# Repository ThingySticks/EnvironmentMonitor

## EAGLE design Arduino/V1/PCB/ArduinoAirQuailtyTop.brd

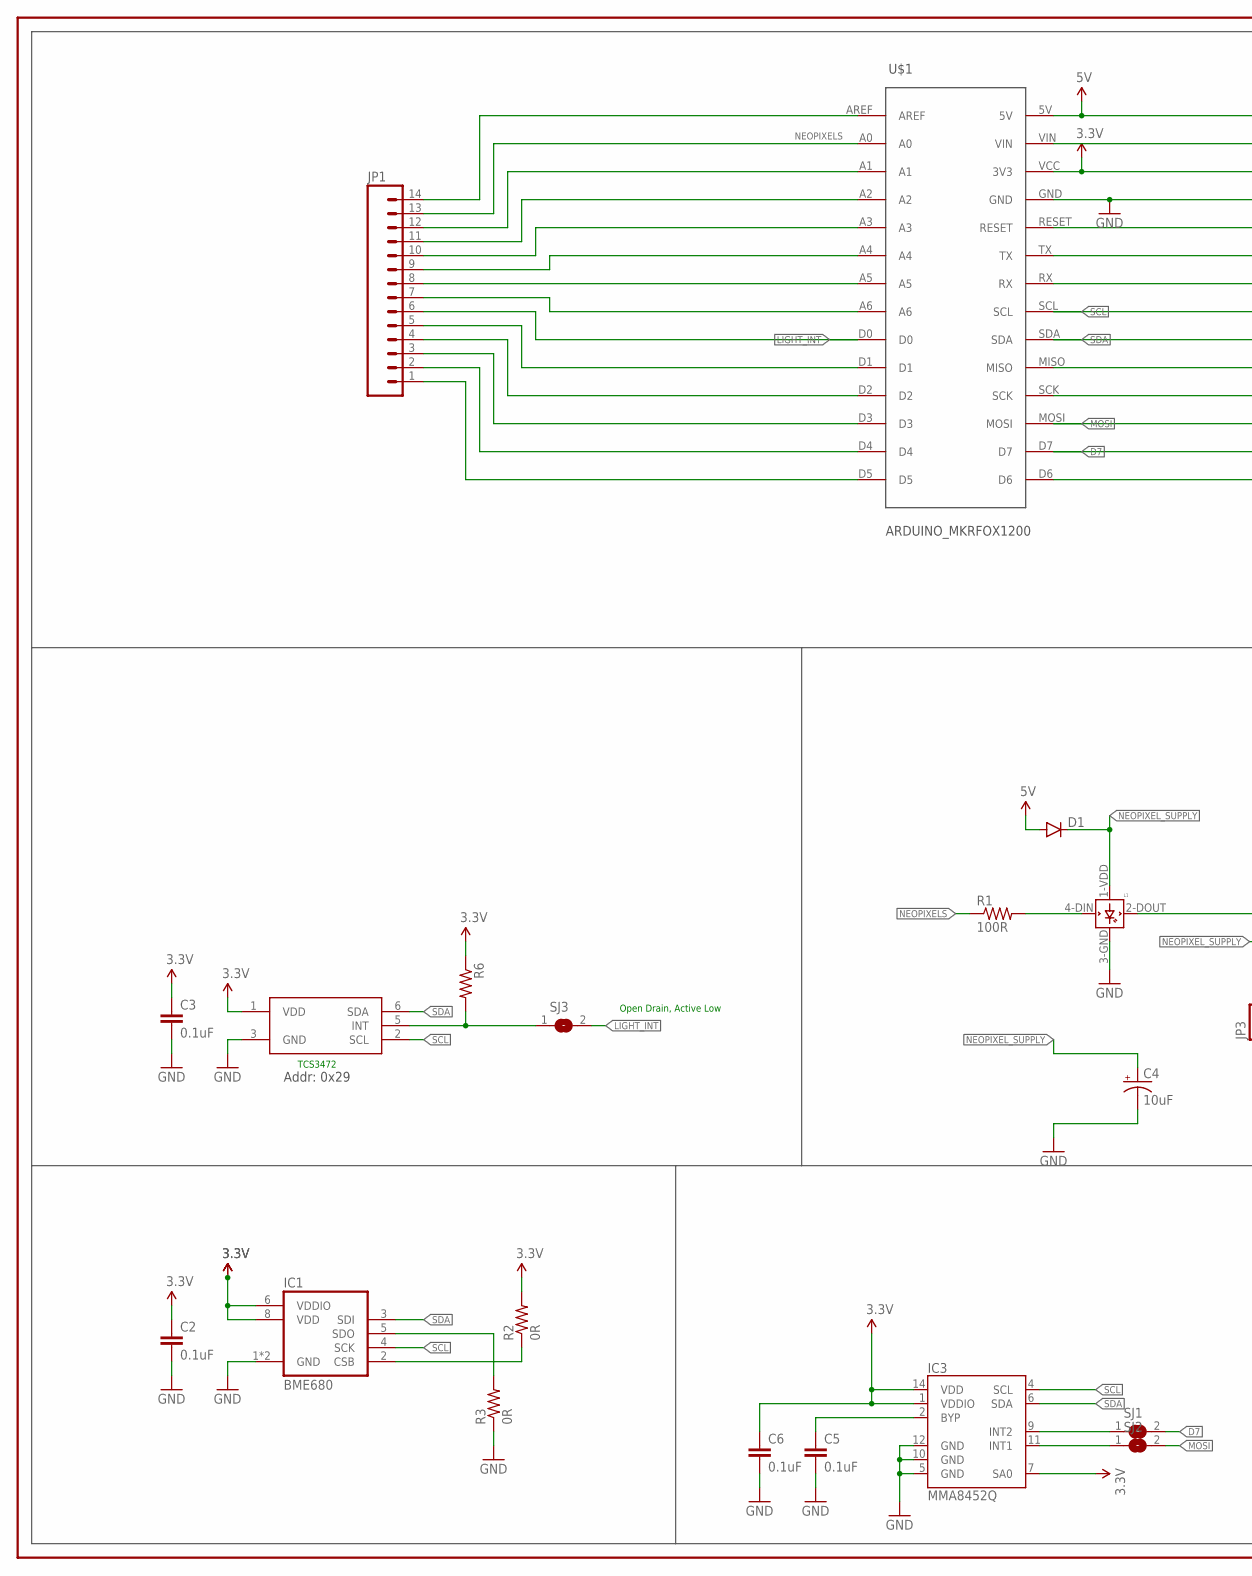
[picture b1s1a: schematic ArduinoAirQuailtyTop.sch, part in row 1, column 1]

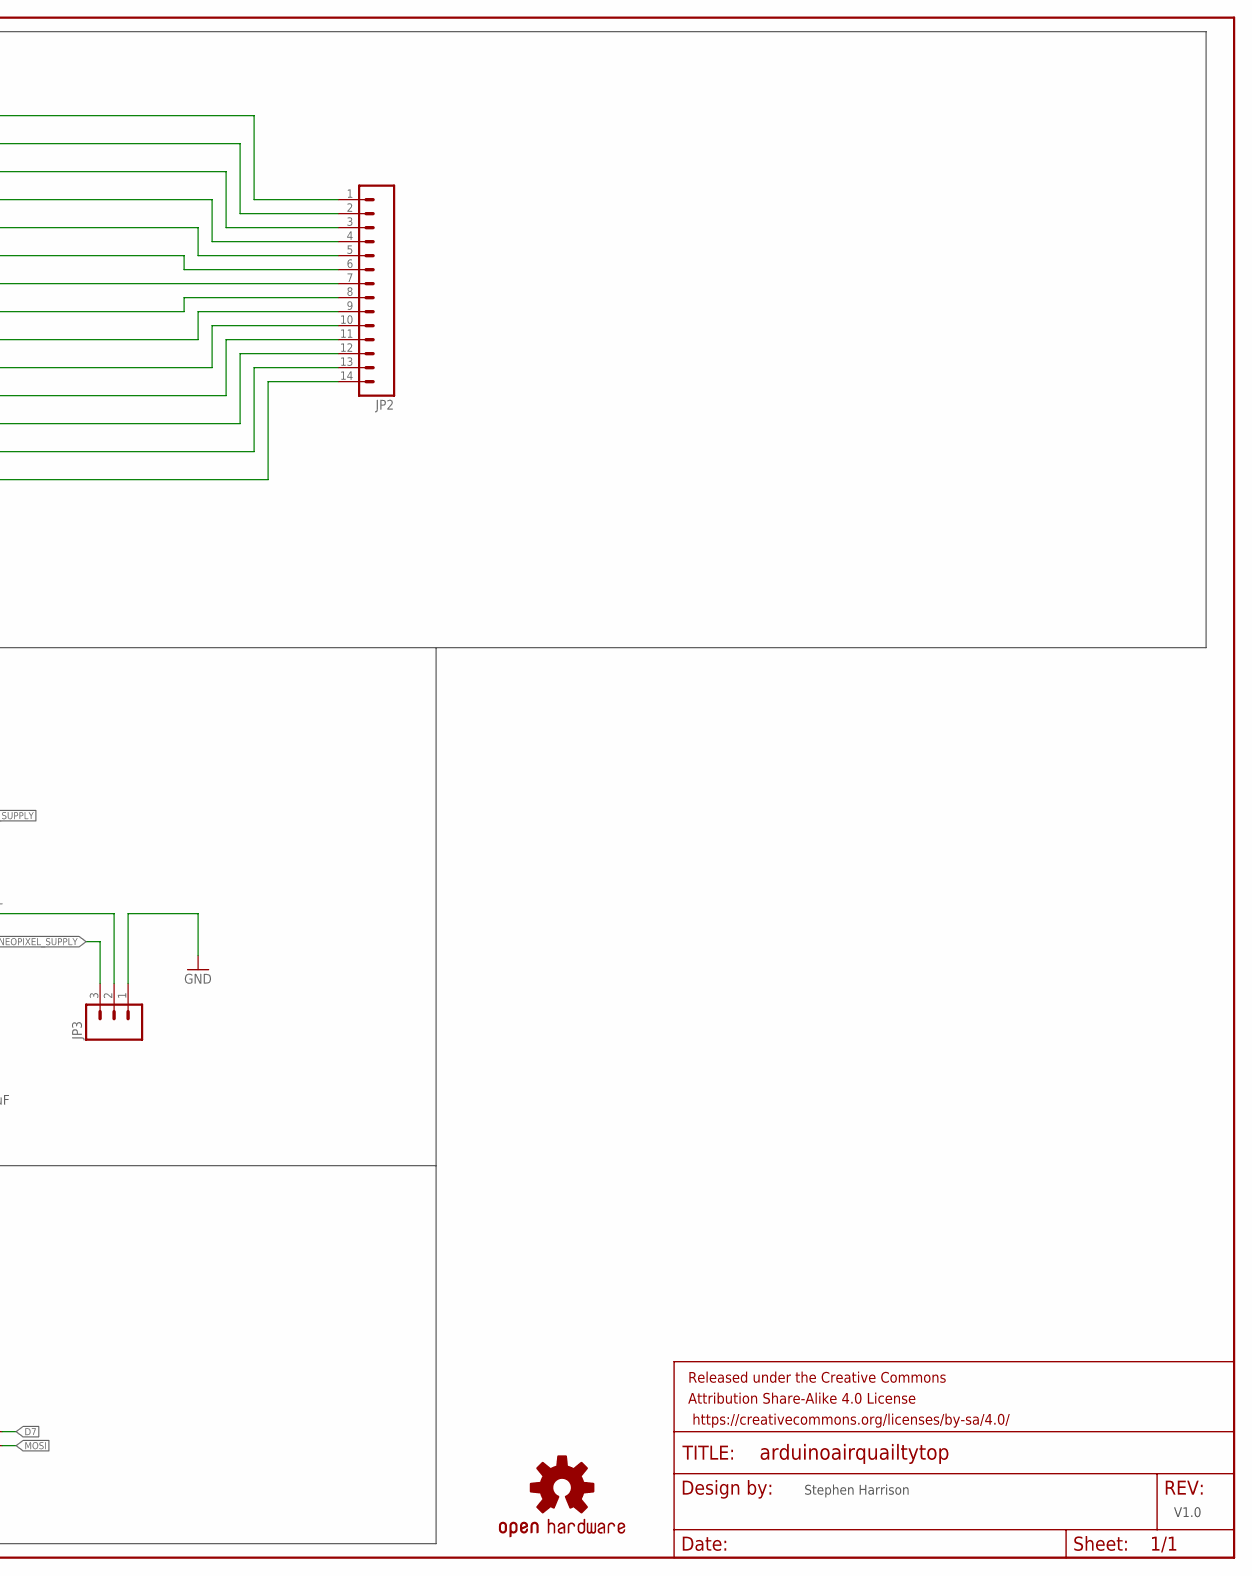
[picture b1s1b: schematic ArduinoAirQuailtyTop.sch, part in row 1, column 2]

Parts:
C2, C3, C5, C6: 0.1uF; 0805
C4: 10uF; EIA3216
D1: DIODESMA; SMA-DIODE
FRAME1: FRAME-LEDGER; CREATIVE_COMMONS
IC1: BME680; MOUSER 262-BME680
IC2: TCS34725FN; FN-6; MOUSER 985-TCS34725FN
IC3: MMA8452Q; QFN-16_0.5MM; MOUSER 841-MMA8452QT
JP1, JP2: M14; 1X14
JP3: M03POLAR; MOLEX-1X3
L1: WS2812B
LOGO1: OSHW-LOGOM; OSHW-LOGO-M
R1: 100R; 0805
R2, R3: 0R; 0805
R6: RESISTOR0805-RES; 0805
SJ1, SJ2, SJ3: SJ
U$1: ARDUINO_MKRFOX1200

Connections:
3.3V: C2.1, C3.1, C6.1, IC1.6 (VDDIO), IC1.8 (VDD), IC2.1 (VDD), IC3.1 (VDDIO), IC3.7 (SA0), IC3.14 (VDD), JP2.3, R2.2, R6.1, U$1.VCC (3V3)
5V: D1.A, JP2.1, U$1.5V
D7: JP2.13, SJ1.2, U$1.D7
GND: C2.2, C3.2, C4.C (-), C5.2, C6.2, IC1.1 (GND), IC1.7 (GND), IC2.3 (GND), IC3.5 (GND), IC3.10 (GND), IC3.12 (GND), JP2.4, JP3.1, L1.3-GND (GND), R3.1, U$1.GND
LIGHT_INT: JP1.6, SJ3.2, U$1.D0
MOSI: JP2.12, SJ2.2, U$1.MOSI
unnamed: IC3.9 (INT2), SJ1.1
unnamed: IC3.11 (INT1), SJ2.1
unnamed: JP1.1, U$1.D5
unnamed: JP1.2, U$1.D4
unnamed: JP1.3, U$1.D3
unnamed: C5.1, IC3.2 (BYP)
unnamed: JP1.4, U$1.D2
unnamed: JP1.5, U$1.D1
unnamed: JP1.7, U$1.A6
unnamed: JP1.8, U$1.A5
unnamed: JP1.9, U$1.A4
unnamed: JP1.10, U$1.A3
unnamed: JP1.11, U$1.A2
unnamed: JP1.12, U$1.A1
unnamed: JP1.14, U$1.AREF
unnamed: JP2.14, U$1.D6
unnamed: JP2.11, U$1.SCK
unnamed: JP2.10, U$1.MISO
unnamed: JP2.7, U$1.RX
unnamed: JP2.6, U$1.TX
unnamed: JP2.5, U$1.RESET
unnamed: JP2.2, U$1.VIN
unnamed: IC1.5 (SDO), R3.2
unnamed: IC1.2 (CSB), R2.1
unnamed: IC2.5 (INT), R6.2, SJ3.1
unnamed: L1.4-DIN (DIN), R1.2
unnamed: JP3.2, L1.2-DOUT (DOUT)
NEOPIXELS: JP1.13, R1.1, U$1.A0
NEOPIXEL_SUPPLY: C4.A (+), D1.C, JP3.3, L1.1-VDD (VDD)
SCL: IC1.4 (SCK), IC2.2 (SCL), IC3.4 (SCL), JP2.8, U$1.SCL
SDA: IC1.3 (SDI), IC2.6 (SDA), IC3.6 (SDA), JP2.9, U$1.SDA

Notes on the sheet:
TCS3472
Open Drain, Active Low
Stephen Harrison
V1.0
Addr: 0x29

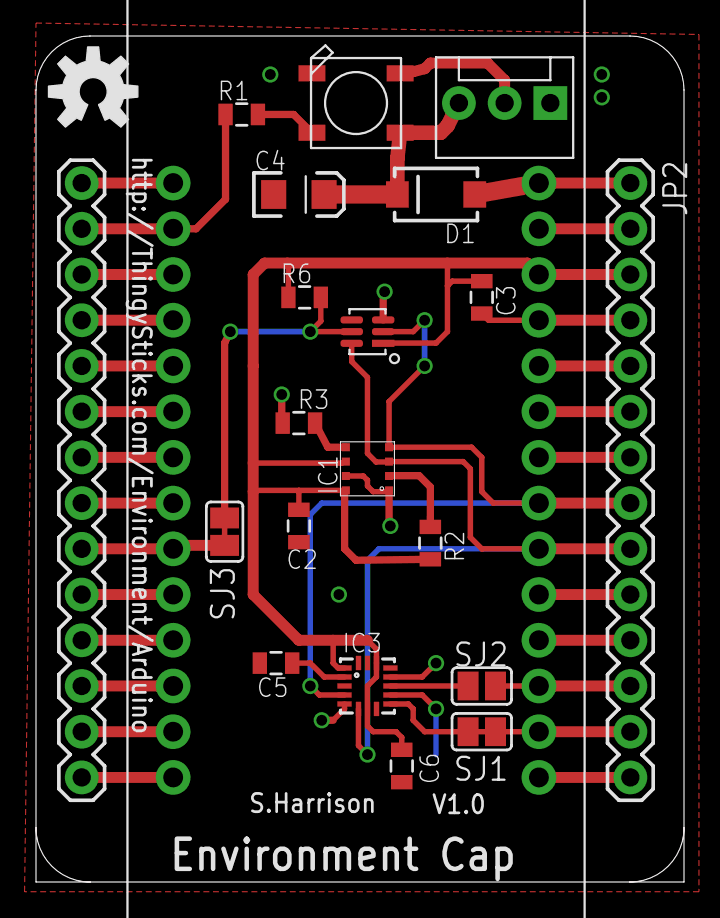
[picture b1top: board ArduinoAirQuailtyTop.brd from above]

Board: 2 copper layers, 36.0 x 47.0 mm, 23 parts (0 on the bottom side), 37 nets.

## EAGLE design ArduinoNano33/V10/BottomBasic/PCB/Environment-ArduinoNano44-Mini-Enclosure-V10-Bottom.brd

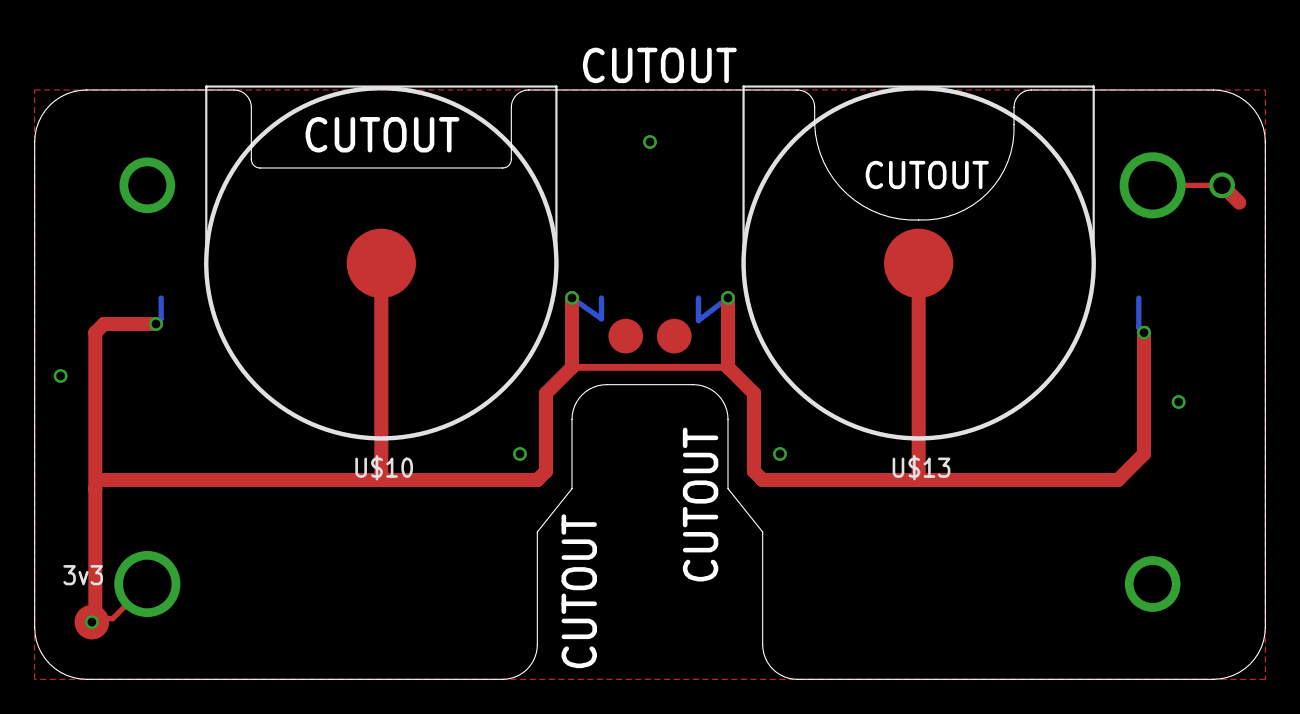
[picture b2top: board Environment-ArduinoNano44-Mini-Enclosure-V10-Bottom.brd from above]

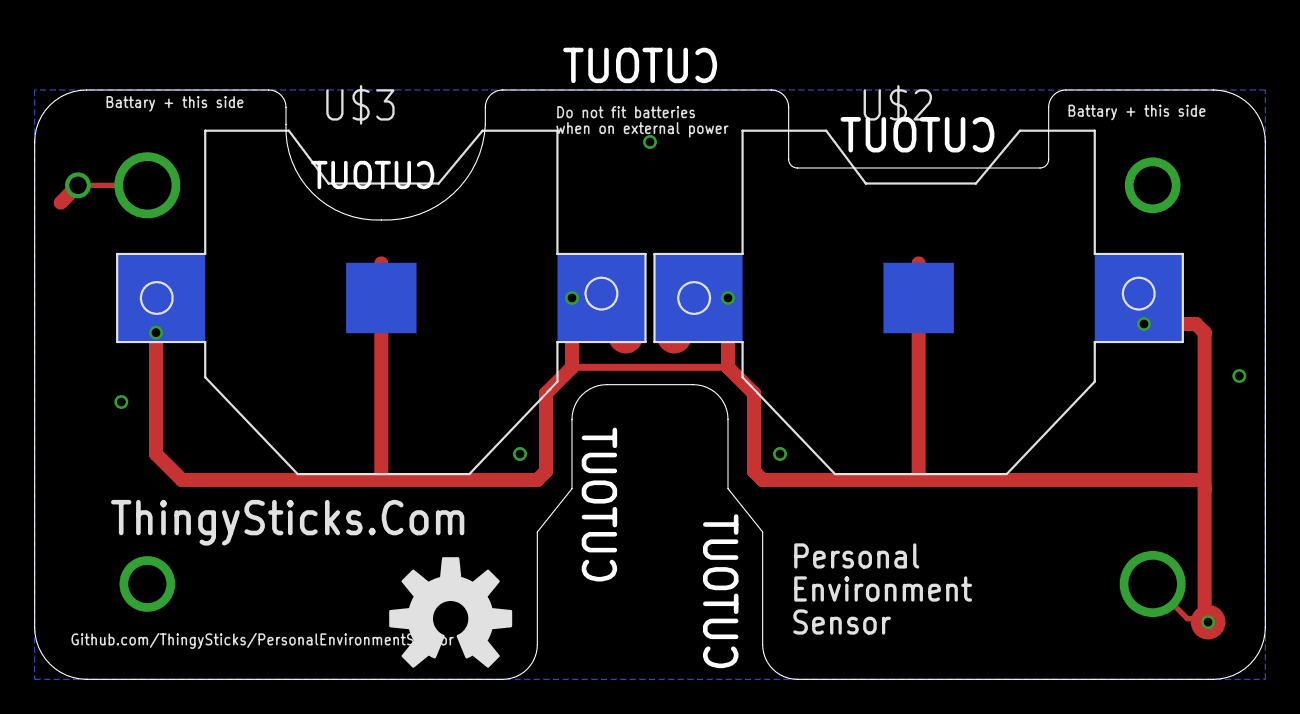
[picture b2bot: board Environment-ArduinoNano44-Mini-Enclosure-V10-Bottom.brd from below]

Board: 2 copper layers, 71.0 x 34.0 mm, 5 parts (5 on the bottom side), 2 nets.

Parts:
LOGO3: OSHW-LOGOL; OSHW-LOGO-L
U$2, U$3: CR2032-SMD
U$10, U$13: CR2032-SPLIT-PCB-POSITIVE; CR2032-SMD-POSITIVE-TERMINAL

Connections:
3.3V: U$2.+$1, U$2.+$2, U$3.+$1, U$3.+$2, U$10.+, U$13.+
GND: U$2.-, U$3.-

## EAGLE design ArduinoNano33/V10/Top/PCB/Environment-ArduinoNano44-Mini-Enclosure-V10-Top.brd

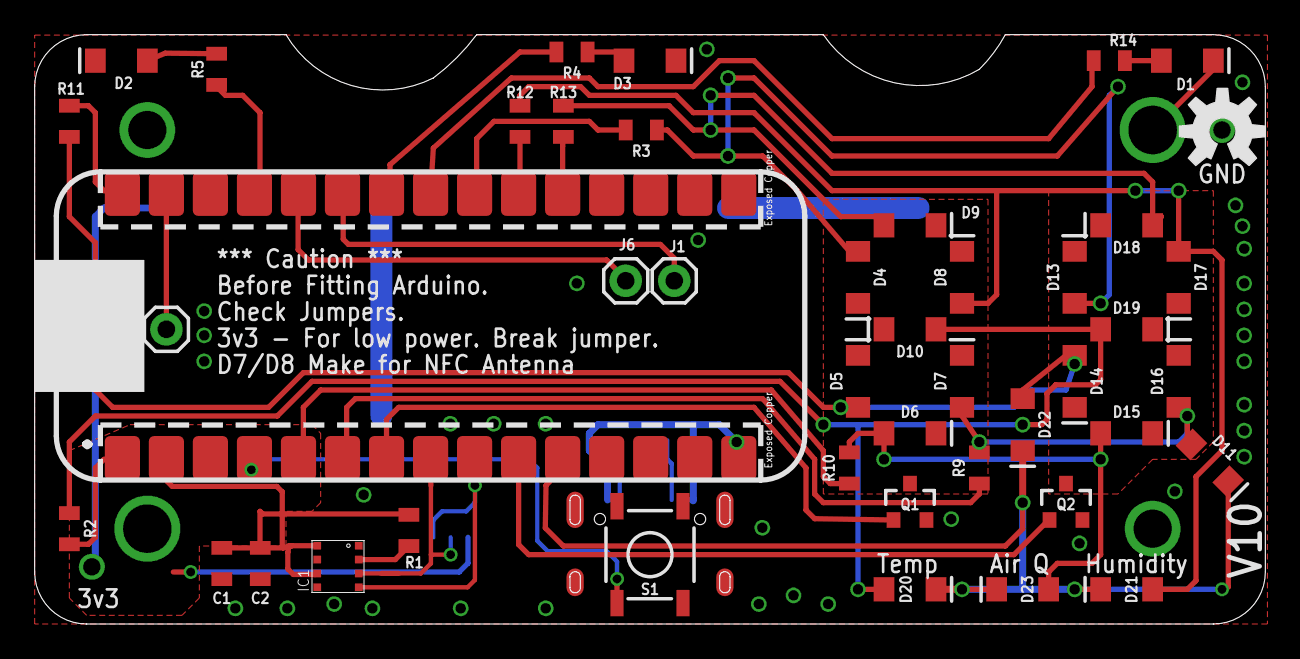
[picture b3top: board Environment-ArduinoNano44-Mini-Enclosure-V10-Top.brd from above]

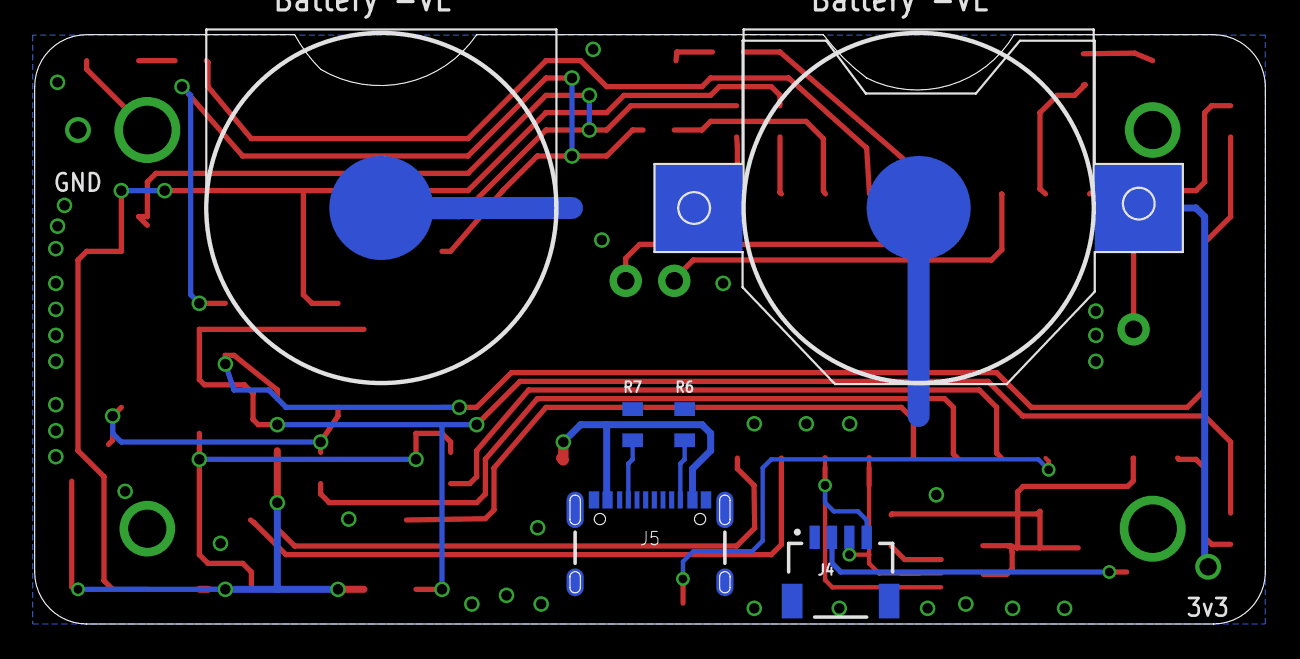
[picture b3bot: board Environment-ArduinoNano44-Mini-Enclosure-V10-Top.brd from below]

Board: 2 copper layers, 71.0 x 34.0 mm, 51 parts (7 on the bottom side), 37 nets.

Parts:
C1: 0.1uF; 0805
C2: 1.0uF; 0805
D1: Red; LED-1206
D2: Yellow; LED-1206
D3, D20, D21, D23: Green; LED-1206
D4, D5, D6, D7, D8, D9, D10, D11, D13, D14, D15, D16, D17, D18, D19, D22: Blue; LED-1206
IC1: BME680
J1, J3, J6: 1X01
J4: QUIC; JST04_1MM_RA
J5: USB-C-16P
LOGO1: OSHW-LOGOM; OSHW-LOGO-M
Q1, Q2: 5.8A/30V/35mΩ; SOT23-3
R1: 10k; 0805
R2, R3, R4, R5, R9, R10, R11, R12, R13, R14: 1k5; 0805
R6, R7: 5k1; 0805
S1: MOMENTARY-SWITCH-SPST-SMD-5.2MM; TACTILE_SWITCH_SMD_5.2MM
U$1: ARDUINO_33_NANOARDUINO_NANO_33_BLE_SENSE_SMD; ARDUINO_NANO_33_SMD
U$6: CR2032-SMD
U$8, U$9: CR2032-SPLIT-PCBCR2032-NEGATIVE; CR2032-SMD-NEGATIVE-TERMINAL

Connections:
3.3V: C1.1, C2.1, IC1.6, IC1.8, J4.2, R1.2, U$1.@2, U$6.+$2
A: D9.A, D18.A, R13.1
A0: S1.1, U$1.@4
B: D8.A, D17.A, D21.A, R12.1
C: D7.A, D11.A, D16.A, R9.2
CC1: J5.A5, R7.1
CC2: J5.B5, R6.1
D: D6.A, D15.A, D23.A, R10.2
DIGIT1: D4.C, D5.C, D6.C, D7.C, D8.C, D9.C, D10.C, Q1.3
DIGIT1_SELECT: Q1.1, U$1.@7
DIGIT2: D13.C, D14.C, D15.C, D16.C, D17.C, D18.C, D19.C, Q2.3
DIGIT2_SELECT: Q2.1, U$1.@10
DIGIT3: D11.C, D20.C, D21.C, D22.C, D23.C, U$1.@11
E: D5.A, D14.A, D22.A, R11.1
F: D4.A, D13.A, R3.1
G: D10.A, D19.A, D20.A, R2.1
GND: C1.2, C2.2, D1.C, D2.C, D3.C, IC1.1, IC1.5, IC1.7, J4.1, J5.GND, J5.GND2, Q1.2, Q2.2, R6.2, R7.2, S1.3, U$1.@14, U$1.@19, U$6.-, U$8.-, U$9.-
GREEN: R4.2, U$1.@24
unnamed: IC1.2, R1.1
unnamed: D1.A, R14.1
unnamed: R9.1, U$1.@6
unnamed: R2.2, U$1.1
unnamed: R11.2, U$1.@30
unnamed: R12.2, U$1.@21
unnamed: R10.1, U$1.@5
unnamed: R13.2, U$1.@20
unnamed: R3.2, U$1.@22
unnamed: D3.A, R4.1
unnamed: D2.A, R5.1
unnamed: J3.1, U$1.@29
NCF_ANTENNA1: J6.1, U$1.@26
NCF_ANTENNA2: J1.1, U$1.@25
RED: R14.2, U$1.@23
SCL: IC1.4, J4.4, U$1.@9
SDA: IC1.3, J4.3, U$1.@8
VIN: J5.VBUS1, J5.VBUS2, U$1.@15
YELLOW: R5.2, U$1.@27

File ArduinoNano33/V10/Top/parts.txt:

Partlist

Exported from Environment-ArduinoNano33-V10.1-Top.brd at 27/02/2020 07:29

EAGLE Version 7.4.0 Copyright (c) 1988-2015 CadSoft

Assembly variant: 

Part     Value                                             Package                        Library                        Position (mm)         Orientation

C1       0.1uF                                             0805                           ThingySticks                   (10.795 3.4925)       R270
C2       1.0uF                                             0805                           ThingySticks                   (13.0175 3.4925)      R270
D1       Red                                               LED-1206                       ThingySticks                   (66.5 32.5)           R0
D2       Green                                             LED-1206                       ThingySticks                   (5 32.5)              R180
D3       Yellow                                            LED-1206                       ThingySticks                   (35.5 32.5)           R0
D4       Blue                                              LED-1206                       ThingySticks                   (47.5 20)             R270
D5       Blue                                              LED-1206                       ThingySticks                   (47.5 14)             R90
D6       Blue                                              LED-1206                       ThingySticks                   (50.5 11)             R0
D7       Blue                                              LED-1206                       ThingySticks                   (53.5 14)             R90
D8       Blue                                              LED-1206                       ThingySticks                   (53.5 20)             R90
D9       Blue                                              LED-1206                       ThingySticks                   (50.5 23)             R0
D10      Blue                                              LED-1206                       ThingySticks                   (50.5 17)             R180
D11      Blue                                              LED-1206                       ThingySticks                   (67.8 9.3)            R315
D13      Blue                                              LED-1206                       ThingySticks                   (60 20)               R90
D14      Blue                                              LED-1206                       ThingySticks                   (60 14)               R270
D15      Blue                                              LED-1206                       ThingySticks                   (63 11)               R0
D16      Blue                                              LED-1206                       ThingySticks                   (66 14)               R90
D17      Blue                                              LED-1206                       ThingySticks                   (66 20)               R270
D18      Blue                                              LED-1206                       ThingySticks                   (63 23)               R180
D19      Blue                                              LED-1206                       ThingySticks                   (63 17)               R0
D20      Green                                             LED-1206                       ThingySticks                   (50.5 2)              R0
D21      Green                                             LED-1206                       ThingySticks                   (63 2)                R180
D22      Blue                                              LED-1206                       ThingySticks                   (57 11.5)             R270
D23      Green                                             LED-1206                       ThingySticks                   (57 2)                R180
IC1      BME680                                            BME680                         ThingySticks                   (17.5 3.3175)         R90
J1                                                         1X01                           SparkFun-Connectors            (36.9 19.8)           R270
J3                                                         1X01                           SparkFun-Connectors            (7.6 17)              R0
J4       QUIC                                              JST04_1MM_RA                   SparkFun-Connectors-2020-01-17 (24.5 5)              MR0
J6                                                         1X01                           SparkFun-Connectors            (34.1 19.8)           R270
JP1      USB-NEW-MICROB                                    USB-MICROB                     Tinamous                       (35.4 3)              MR0
Q1       5.8A/30V/35m?                                     SOT23-3                        SparkFun-DiscreteSemi          (50.5 7)              R0
Q2       5.8A/30V/35m?                                     SOT23-3                        SparkFun-DiscreteSemi          (59.5 7)              R0
R1       10k                                               0805                           SparkFun-Resistors             (21.59 4.7975)        R90
R2       1k5                                               0805                           SparkFun-Resistors             (2 5.5)               R270
R3       1k5                                               0805                           SparkFun-Resistors             (35 28.8175)          R180
R4       1k5                                               0805                           SparkFun-Resistors             (31 33)               R180
R5       1k5                                               0805                           SparkFun-Resistors             (10.5 32)             R270
R6       200k                                              0805                           SparkFun-Resistors             (27.25 2.25)          R90
R7       100k                                              0805                           SparkFun-Resistors             (29.9 2.95)           R0
R9       1k5                                               0805                           SparkFun-Resistors             (54.5 9)              R90
R10      1k5                                               0805                           SparkFun-Resistors             (47 9)                R90
R11      1k5                                               0805                           SparkFun-Resistors             (2 29)                R90
R12      1k5                                               0805                           SparkFun-Resistors             (28 29)               R270
R13      1k5                                               0805                           SparkFun-Resistors             (30.5 29)             R270
R14      1k5                                               0805                           SparkFun-Resistors             (62 32.5)             R180
U$1      ARDUINO_33_NANOARDUINO_NANO_33_BLE_SENSE_SMD_WIDE ARDUINO_NANO_33_SMD_WIDER_PADS ThingySticks                   (1.25 8.305)          R90
U$6                                                        CR2032-SMD                     ThingySticks                   (20 24)               MR0
U$8      CR2032-SPLIT-PCBCR2032-NEGATIVE                   CR2032-SMD-NEGATIVE-TERMINAL   ThingySticks                   (20 24)               MR0
U$9      CR2032-SPLIT-PCBCR2032-NEGATIVE                   CR2032-SMD-NEGATIVE-TERMINAL   ThingySticks                   (51 24)               MR0

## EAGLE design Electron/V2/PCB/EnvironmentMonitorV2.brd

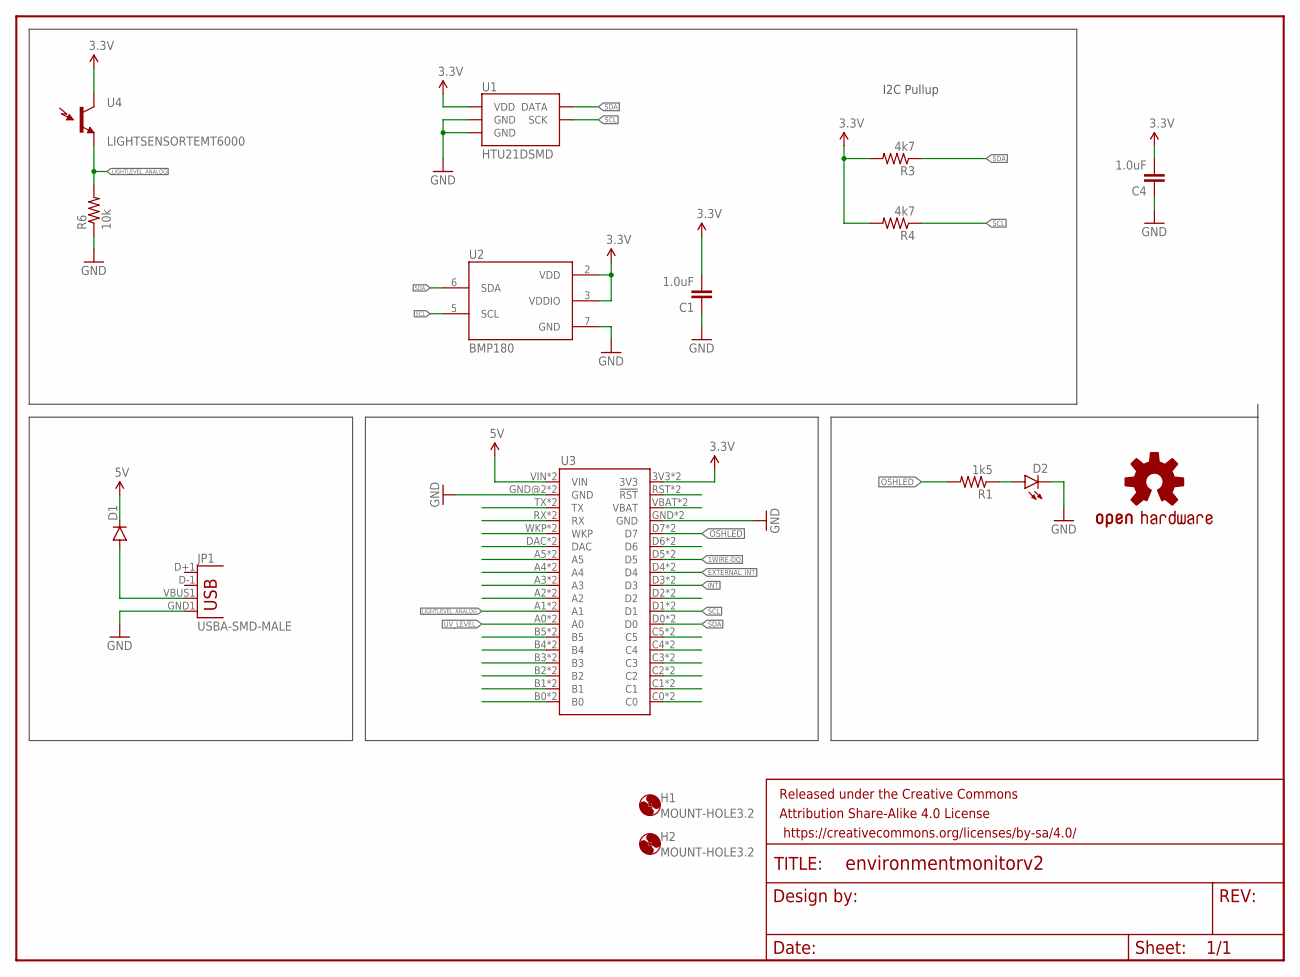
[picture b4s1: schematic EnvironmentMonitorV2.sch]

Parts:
C1, C4: 1.0uF; 0805-CAP
D1: DIODESMA; SMA-DIODE
D2: LED1206-BOTTOM; LED-1206-BOTTOM
FRAME1: FRAME-LETTER; CREATIVE_COMMONS
H1, H2: MOUNT-HOLE3.2; 3,2
JP1: USBA-SMD-MALE; USB-A-SMT-MALE
LOGO1: OSHW-LOGOM; OSHW-LOGO-M
R1: 1k5; 0805
R3, R4: 4k7; 0805
R6: 10k; 0805
U1: HTU21DSMD; HTU21D
U2: BMP180
U3: ELECTRONDUALNAMED; ELECTRON_SIMPLE_SILK_NAMES_DUAL
U4: LIGHTSENSORTEMT6000; TEMT6000-SEN

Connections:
1WIRE-DQ: U3.D5, U3.D5_1 (D5)
3.3V: C1.2, C4.2, R3.2, R4.2, U1.VDD, U2.2 (VDD), U2.3 (VDDIO), U3.3V3, U3.3V3_1 (3V3), U4.COLLECTOR (C1)
5V: D1.C, U3.VIN, U3.VIN_1B (VIN)
EXTERNAL_INT: U3.D4, U3.D4_1 (D4)
GND: C1.1, C4.1, D2.C, JP1.GND1 (GND), R6.1, U1.7 (GND), U1.GND, U2.7 (GND), U3.GND, U3.GND@2 (GND), U3.GND_1 (GND), U3.GND_1B (GND)
INT: U3.D3, U3.D3_1 (D3)
LIGHTLEVEL_ANALOG: R6.2, U3.A1, U3.A1_1 (A1), U4.EMITTER (E1)
unnamed: U3.RST (!RST), U3.RST_1 (!RST)
unnamed: U3.VBAT, U3.VBATT_1 (VBAT)
unnamed: U3.D6, U3.D6_1 (D6)
unnamed: D1.A, JP1.VBUS1 (VBUS)
unnamed: D2.A, R1.1
unnamed: U3.D2, U3.D2_1 (D2)
unnamed: U3.C5, U3.C5_1 (C5)
unnamed: U3.C4, U3.C4_1 (C4)
unnamed: U3.C3, U3.C3_1 (C3)
unnamed: U3.C2, U3.C2_1 (C2)
unnamed: U3.C1, U3.C1_1 (C1)
unnamed: U3.C0, U3.C0_1 (C0)
unnamed: U3.B0, U3.B0_1 (B0)
unnamed: U3.B1, U3.B1_1 (B1)
unnamed: U3.B2, U3.B2_1 (B2)
unnamed: U3.B3, U3.B3_1 (B3)
unnamed: U3.B4, U3.B4_1 (B4)
unnamed: U3.B5, U3.B5_1 (B5)
unnamed: U3.A2, U3.A2_1 (A2)
unnamed: U3.A3, U3.A3_1 (A3)
unnamed: U3.A4, U3.A4_1 (A4)
unnamed: U3.A5, U3.A5_1 (A5)
unnamed: U3.DAC, U3.DAC_1 (DAC)
unnamed: U3.WKP, U3.WKP_1 (WKP)
unnamed: U3.RX, U3.RX_1 (RX)
unnamed: U3.TX, U3.TX_1 (TX)
OSHLED: R1.2, U3.D7, U3.D7_1 (D7)
SCL: R4.1, U1.SCK, U2.5 (SCL), U3.D1, U3.D1_1 (D1)
SDA: R3.1, U1.DATA, U2.6 (SDA), U3.D0, U3.D0_1 (D0)
UV_LEVEL: U3.A0, U3.A0_1 (A0)

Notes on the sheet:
I2C Pullup

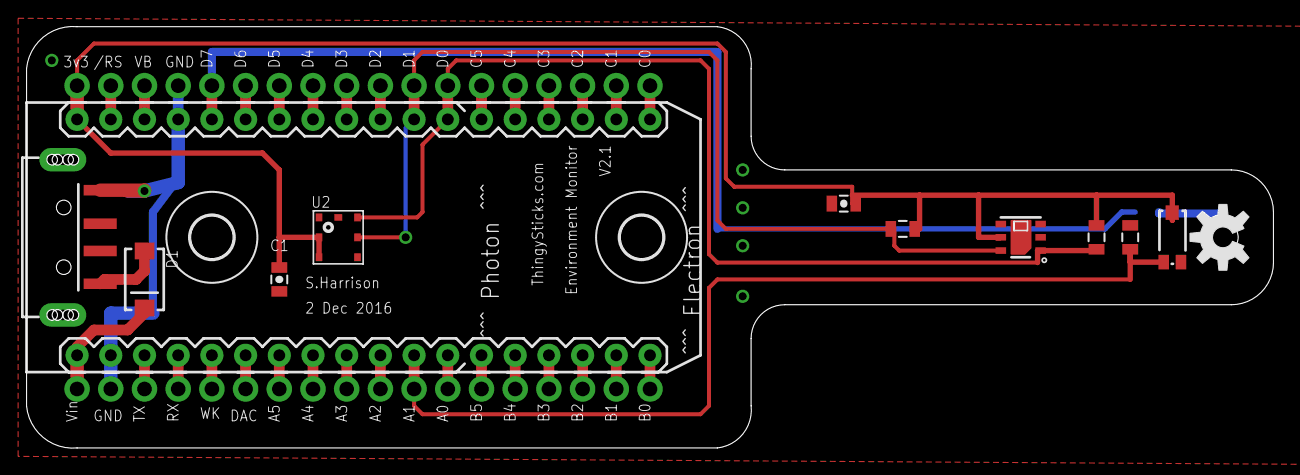
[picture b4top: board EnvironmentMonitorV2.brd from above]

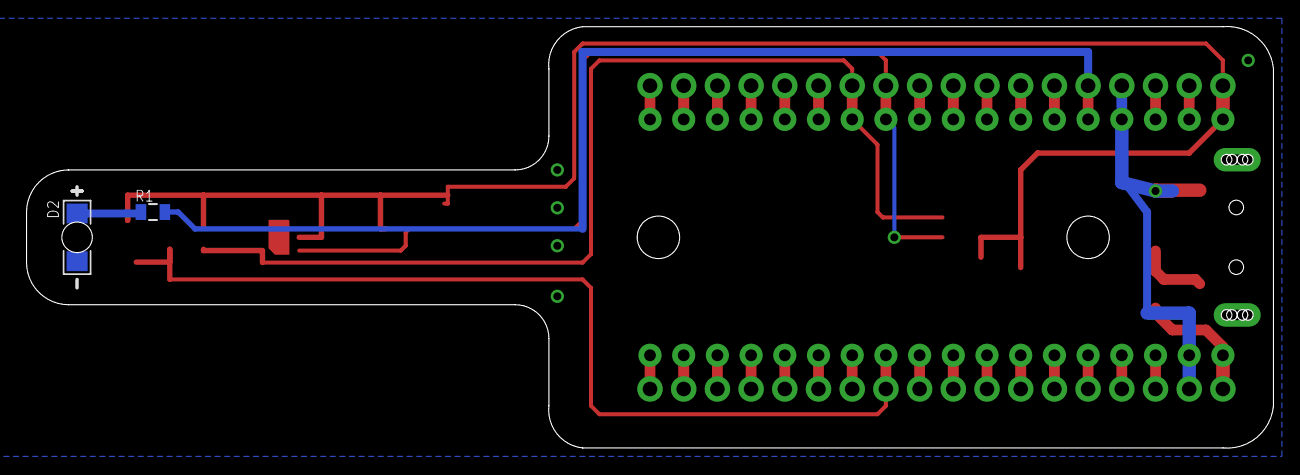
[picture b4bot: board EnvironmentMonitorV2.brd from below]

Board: 2 copper layers, 94.0 x 31.8 mm, 17 parts (2 on the bottom side), 37 nets.

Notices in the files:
parts and their libraries:
SparkFun-Connectors: Licensing: Creative Commons ShareAlike 4.0 International - https://creativecommons.org/licenses/by-sa/4.0
SparkFun-Aesthetics: Released under the Creative Commons Attribution Share-Alike 4.0 License
SparkFun-Aesthetics: https://creativecommons.org/licenses/by-sa/4.0
